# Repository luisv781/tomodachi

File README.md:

# Tomodachi
Tomodachi is a handheld companion inspired by Tamagotchi with Wi-Fi. Your Tomodachi will allow you to set alarms and manage your calendar, but you must also take care of it.
I'm building this project because I've never had my own Tamagotchi, and making my own is better than buying one.

| Schematic | PCB | Case |
|-----------|-----|------|
|  |  |  |

## Bill of Materials
- Seeed Studio XIAO ESP32-C3
- 1.5-inch 128x128 SH1107 Screen
- 3x Tactile Push Buttons
- 1x 4 Position Female Header
- 4x M2x3x4 Heatset Inserts
- 4x M2x12 Screws
- 4x M2.2x6 Screws
- 1x Case (2 3D-Printed Parts)

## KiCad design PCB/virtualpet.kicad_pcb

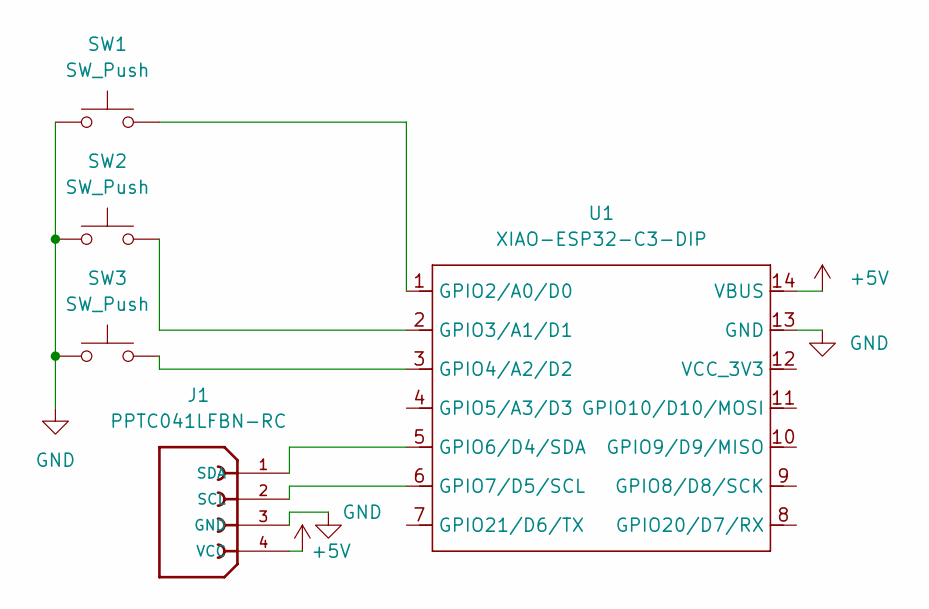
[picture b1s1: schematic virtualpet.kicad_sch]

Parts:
J1: PPTC041LFBN-RC; OLED 128x128; PARTREV J - 04/15/2015
SW1, SW2, SW3: SW_Push; button_12mm
U1: XIAO-ESP32-C3-DIP; XIAO-ESP32C3-DIP

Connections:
+5V: J1.4 (VCC), U1.14 (VBUS)
GND: J1.3 (GND), SW1.1, SW2.1, SW3.1, U1.13 (GND)
unnamed: J1.2 (SCL), U1.6 (GPIO7/D5/SCL)
unnamed: J1.1 (SDA), U1.5 (GPIO6/D4/SDA)
unnamed: SW1.2, U1.1 (GPIO2/A0/D0)
unnamed: SW2.2, U1.2 (GPIO3/A1/D1)
unnamed: SW3.2, U1.3 (GPIO4/A2/D2)

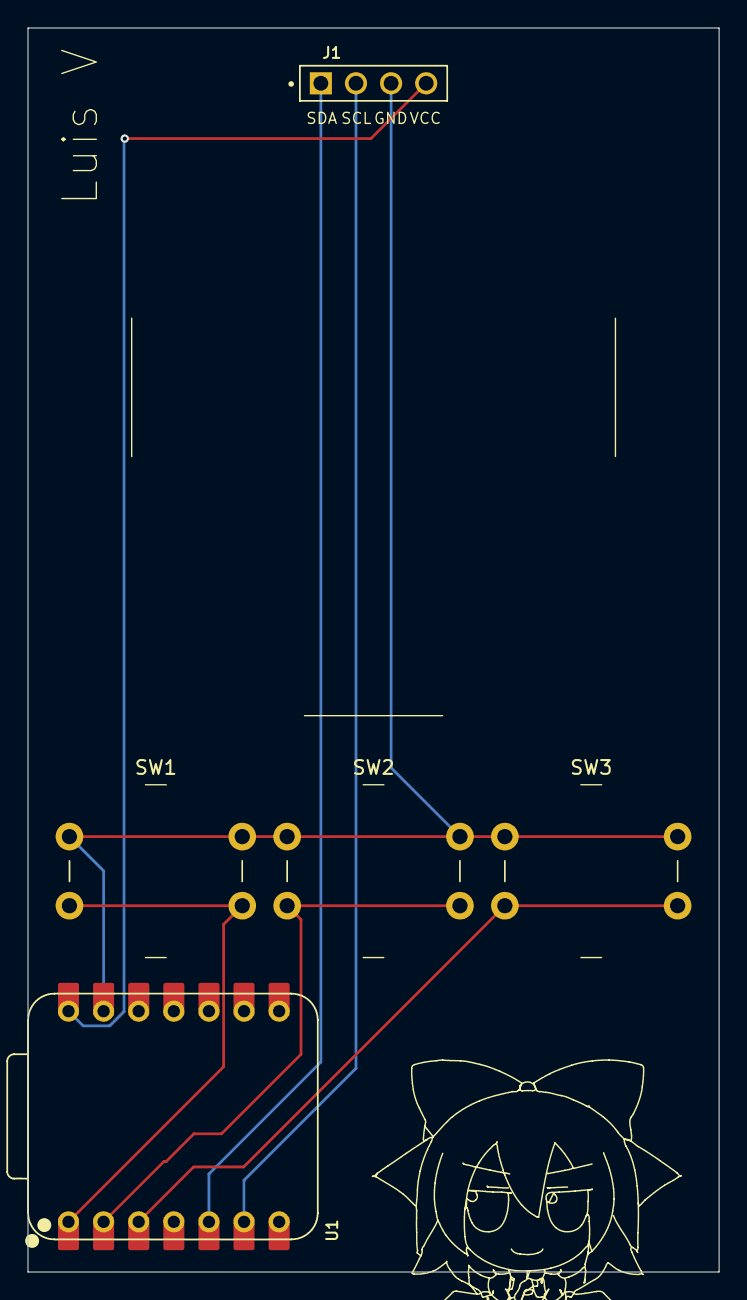
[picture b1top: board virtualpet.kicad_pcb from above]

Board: 2 copper layers, 50.0 x 90.0 mm, 5 parts (0 on the bottom side), 7 nets.

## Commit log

2026-01-14 PCB + CAD
2026-01-16 BOM + Updated CAD & PCB
2026-01-16 README
2026-01-18 Created Firmware
2026-01-18 Source design file
2026-01-18 Updated BOM
2026-01-20 Responsive Buttons
2026-01-28 Update BOM in README
2026-01-28 Update BOM
2026-01-28 Updated CAD Files
2026-02-01 Fixed BOM.csv
